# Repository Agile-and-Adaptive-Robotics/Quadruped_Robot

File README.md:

# AARL Quadruped Robot - Muscle Mutt

## Summary
This repository contains files relevant to the design, analysis, and testing of AARL's canine-inspired quadruped robot named Muscle Mutt.  Our goal in developing Muscle Mutt is for it to serve as a biologically relevant platform for testing embodied synthetic nervous systems pertaining to legged locomotion.  Toward this end, Muscle Mutt features body proportions similar to that of a Whippet, antagonistic pairs of braided pneumatic actuators (BPAs) that serve as proxies for muscles, and a CPG based neural control scheme.  All aspects of Muscle Mutt's design are under active development, including adjusting passive limb dynamics to be congruent with animal models, updating the electrical subsystem to incorporate a wider array of biologically relevant sensory feedback, and designing neural algorithms to generate stable and robust locomotion.

## References
More details on the design and testing of Muscle Mutt can be found in our associated papers.
```
@article{
C. W. Scharzenberger, “Design of a Canine Inspired Quadruped Robot as a Platform for Synthetic Neural Network Control,” Master’s Thesis, Portland State University, Digital, 2019. Accessed: Jun. 18, 2023. [Online]. Available: https://www.proquest.com/docview/2289587100?pq-origsite=gscholar&fromopenview=true
}
```
[Link to paper](https://pdxscholar.library.pdx.edu/cgi/viewcontent.cgi?article=6210&context=open_access_etds)

## Install Instructions
As a comprehensive robotics project, this repository contains information pertaining to three major areas of product development, including: (1) mechanical design, (2) electrical design, and (3) software.  The mechancial design for this project has been completed in Solidworks, while the electrical design has been completed in Eagle.  High level control software has primarily been developed in Matlab, though more recent efforts have been conducted in Python.  Requiste python modules are provided in requirement files in relevant directories.

## Repository Organization
This repository is organized into six primary directories, including: (1) Animatlab, (2) CAD_Electrical, (3) CAD_Mechanical, (4) Code, (5) Documentation, and (6) Manufacturing.  The names of these directories are largely self explanatory, with Animatlab neuromechanical simulations being stored in the Animatlab folder; Eagle CAD documents in the CAD_Electrical folder; Solidworks CAD documents in the CAD_Mechanical folder; Matlab, Python, and C code in the Code folder; supporting documentation and datasheets in the Documentation folder; and 3D printing documentation in the Manufacturing folder.

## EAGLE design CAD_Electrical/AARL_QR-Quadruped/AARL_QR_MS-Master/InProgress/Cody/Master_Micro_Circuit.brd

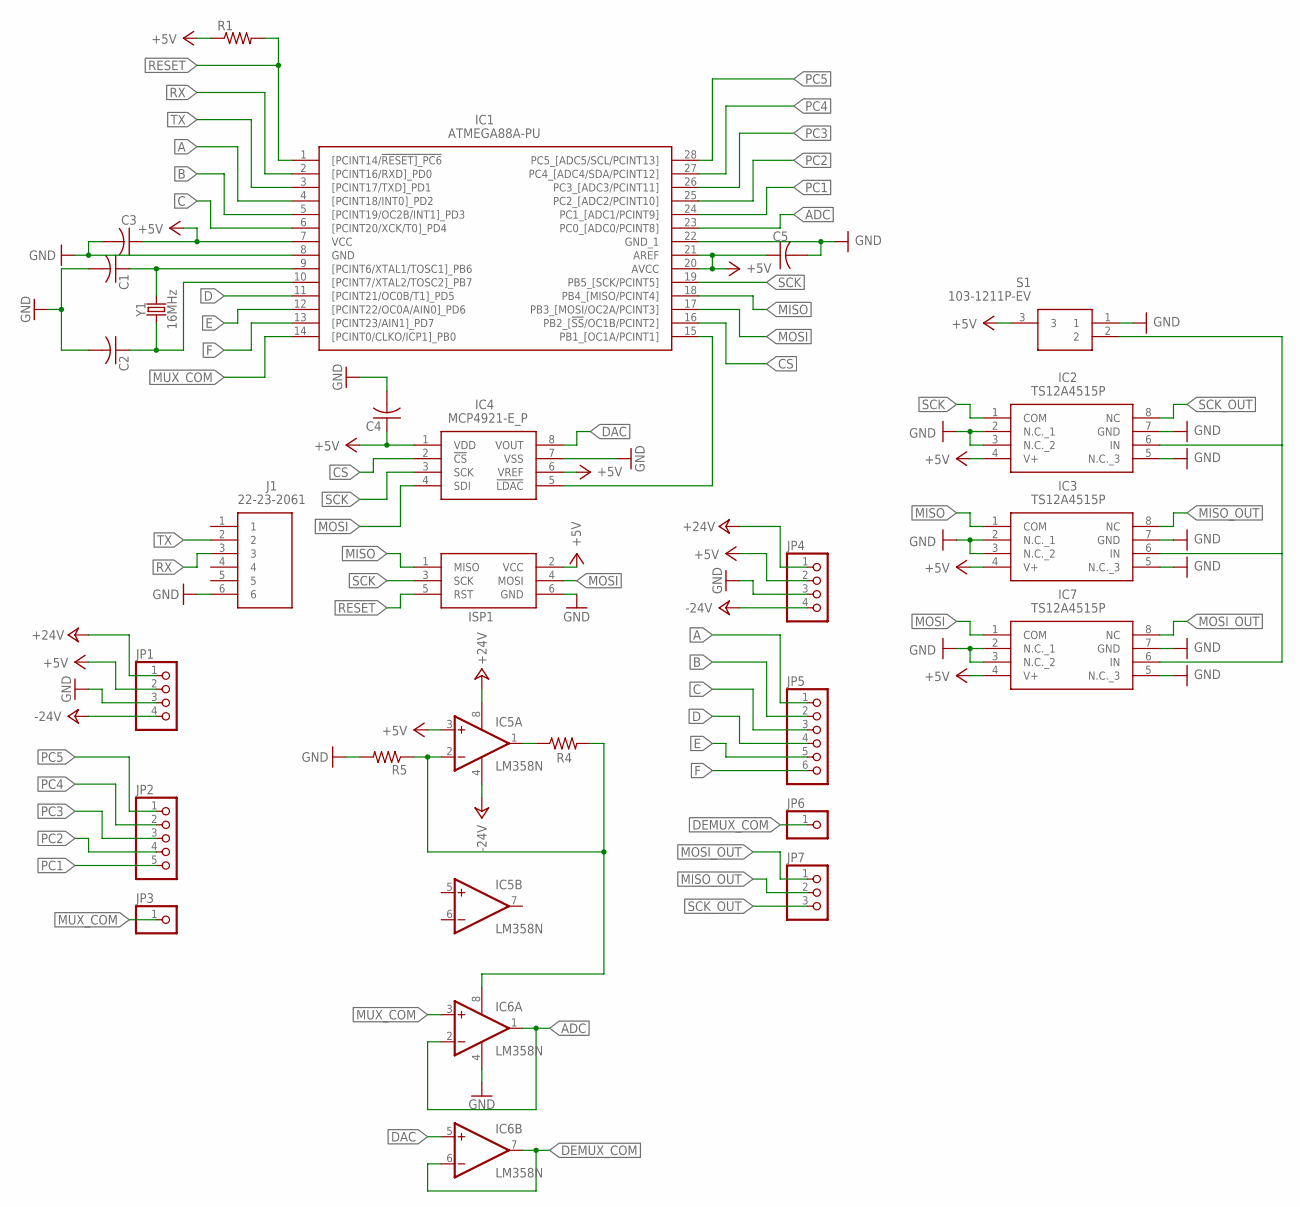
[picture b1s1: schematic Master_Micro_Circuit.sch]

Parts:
C1, C2, C3, C4, C5: C-US050-030X075; C050-030X075
IC1: ATMEGA88A-PU; DIP794W53P254L3467H457Q28N
IC2, IC3, IC7: TS12A4515P; DIP794W46P254L959H508Q8N
IC4: MCP4921-E_P; DIP781W56P254L950H533Q8N
IC5, IC6: LM358N; DIL08
ISP1: AVRISP-BOX
J1: 22-23-2061; SHDR6W87P0X254_1X6_1509X635X10
JP1, JP4: PINHD-1X4; 1X04
JP2: PINHD-1X5; 1X05
JP3, JP6: PINHD-1X1; 1X01
JP5: PINHD-1X6; 1X06
JP7: PINHD-1X3; 1X03
R1, R4, R5: R-US_0207/10; 0207/10
S1: 103-1211P-EV; 1031211PEV
Y1: 16MHz; HC49US

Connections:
+5V: C3.1, C4.1, C5.1, IC1.7 (VCC), IC1.20 (AVCC), IC1.21 (AREF), IC2.4 (V+), IC3.4 (V+), IC4.1 (VDD), IC4.6 (VREF), IC5.3 (+IN), IC7.4 (V+), ISP1.2 (VCC), JP1.2, JP4.2, R1.1, S1.3
+24V: IC5.8 (V+), JP1.1, JP4.1
-24V: IC5.4 (V-), JP1.4, JP4.4
A: IC1.4 ([PCINT18/INT0]_PD2), JP5.1
ADC: IC1.23 (PC0_[ADC0/PCINT8]), IC6.1 (OUT), IC6.2 (-IN)
B: IC1.5 ([PCINT19/OC2B/INT1]_PD3), JP5.2
C: IC1.6 ([PCINT20/XCK/T0]_PD4), JP5.3
CS: IC1.16 (PB2_[!SS!/OC1B/PCINT2]), IC4.2 (!CS)
D: IC1.11 ([PCINT21/OC0B/T1]_PD5), JP5.4
DAC: IC4.8 (VOUT), IC6.5 (+IN)
DEMUX_COM: IC6.6 (-IN), IC6.7 (OUT), JP6.1
E: IC1.12 ([PCINT22/OC0A/AIN0]_PD6), JP5.5
F: IC1.13 ([PCINT23/AIN1]_PD7), JP5.6
GND: C1.2, C2.2, C3.2, C4.2, C5.2, IC1.8 (GND), IC1.22 (GND_1), IC2.2 (N.C._1), IC2.3 (N.C._2), IC2.5 (N.C._3), IC2.7 (GND), IC3.2 (N.C._1), IC3.3 (N.C._2), IC3.5 (N.C._3), IC3.7 (GND), IC4.7 (VSS), IC6.4 (V-), IC7.2 (N.C._1), IC7.3 (N.C._2), IC7.5 (N.C._3), IC7.7 (GND), ISP1.6 (GND), J1.6, JP1.3, JP4.3, R5.2, S1.1
MISO: IC1.18 (PB4_[MISO/PCINT4]), IC3.1 (COM), ISP1.1 (MISO)
MISO_OUT: IC3.8 (NC), JP7.2
MOSI: IC1.17 (PB3_[MOSI/OC2A/PCINT3]), IC4.4 (SDI), IC7.1 (COM), ISP1.4 (MOSI)
MOSI_OUT: IC7.8 (NC), JP7.1
MUX_COM: IC1.14 ([PCINT0/CLKO/ICP1]_PB0), IC6.3 (+IN), JP3.1
unnamed: C2.1, IC1.10 ([PCINT7/XTAL2/TOSC2]_PB7), Y1.1
unnamed: IC5.1 (OUT), R4.1
unnamed: IC2.6 (IN), IC3.6 (IN), IC7.6 (IN), S1.2
unnamed: IC5.2 (-IN), IC6.8 (V+), R4.2, R5.1
unnamed: IC1.15 (PB1_[OC1A/PCINT1]), IC4.5 (!LDAC)
unnamed: C1.1, IC1.9 ([PCINT6/XTAL1/TOSC1]_PB6), Y1.2
PC1: IC1.24 (PC1_[ADC1/PCINT9]), JP2.5
PC2: IC1.25 (PC2_[ADC2/PCINT10]), JP2.4
PC3: IC1.26 (PC3_[ADC3/PCINT11]), JP2.3
PC4: IC1.27 (PC4_[ADC4/SDA/PCINT12]), JP2.2
PC5: IC1.28 (PC5_[ADC5/SCL/PCINT13]), JP2.1
RESET: IC1.1 ([PCINT14/!RESET]_PC6), ISP1.5 (RST), R1.2
RX: IC1.2 ([PCINT16/RXD]_PD0), J1.3
SCK: IC1.19 (PB5_[SCK/PCINT5]), IC2.1 (COM), IC4.3 (SCK), ISP1.3 (SCK)
SCK_OUT: IC2.8 (NC), JP7.3
TX: IC1.3 ([PCINT17/TXD]_PD1), J1.2

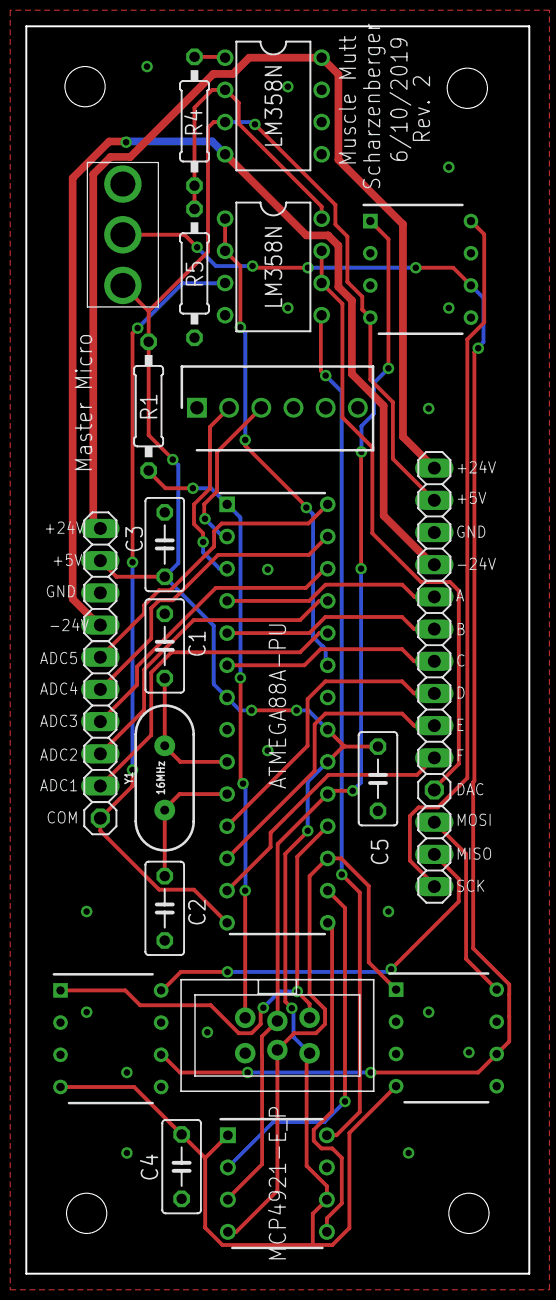
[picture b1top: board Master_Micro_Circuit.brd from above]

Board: 2 copper layers, 39.7 x 98.4 mm, 26 parts (0 on the bottom side), 35 nets.

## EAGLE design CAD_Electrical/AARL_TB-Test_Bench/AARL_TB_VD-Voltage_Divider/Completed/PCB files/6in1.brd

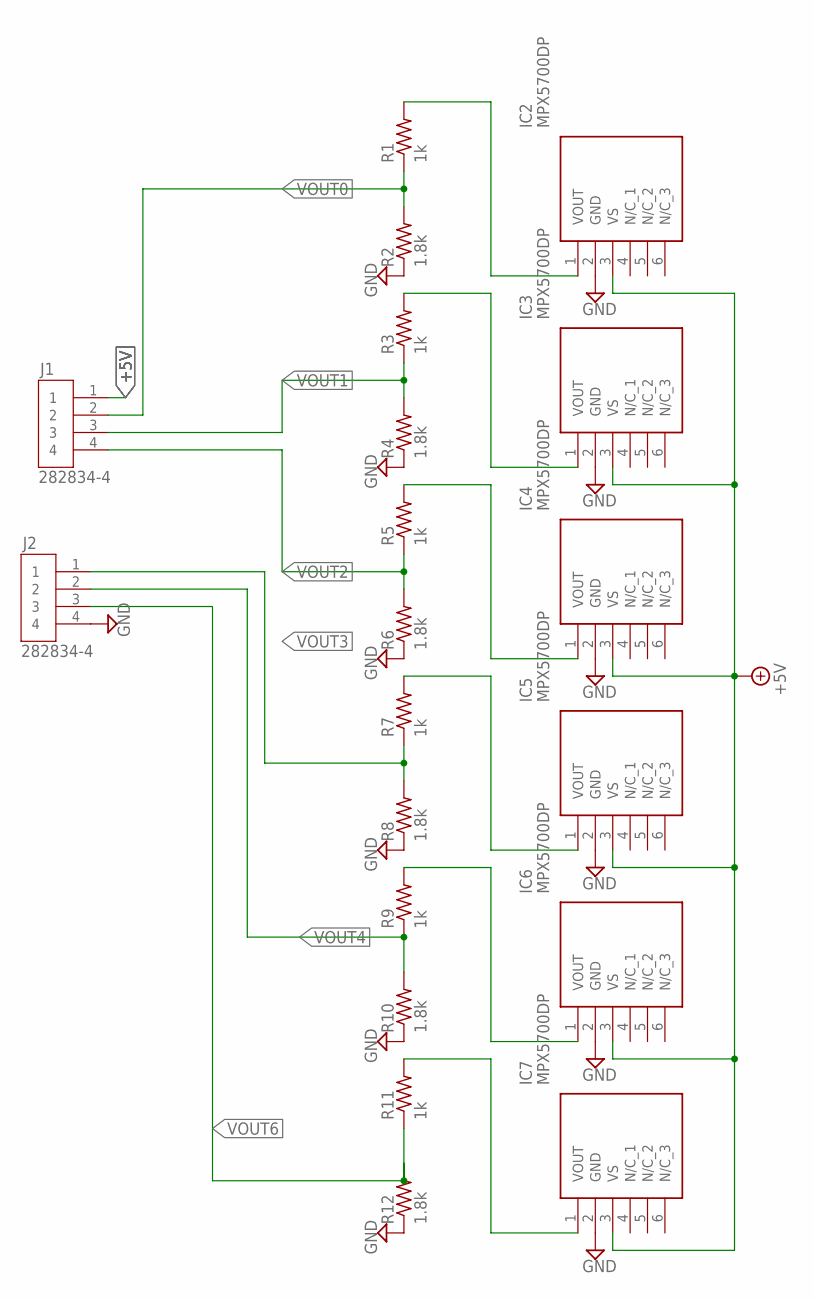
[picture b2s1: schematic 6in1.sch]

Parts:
IC2, IC3, IC4, IC5, IC6, IC7: MPX5700DP
J1, J2: 282834-4; HDRV4W85P254_4X1_1062X650X1000
R1, R3, R5, R7, R9, R11: 1k; 0204V
R2, R4, R6, R8, R10, R12: 1.8k; 0204V

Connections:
+5V: IC2.3 (VS), IC3.3 (VS), IC4.3 (VS), IC5.3 (VS), IC6.3 (VS), IC7.3 (VS), J1.1
GND: IC2.2 (GND), IC3.2 (GND), IC4.2 (GND), IC5.2 (GND), IC6.2 (GND), IC7.2 (GND), J2.4, R2.1, R4.1, R6.1, R8.1, R10.1, R12.1
unnamed: IC2.1 (VOUT), R1.2
unnamed: IC3.1 (VOUT), R3.2
unnamed: IC4.1 (VOUT), R5.2
unnamed: IC5.1 (VOUT), R7.2
unnamed: IC6.1 (VOUT), R9.2
unnamed: IC7.1 (VOUT), R11.2
VOUT0: J1.2, R1.1, R2.2
VOUT1: J1.3, R3.1, R4.2
VOUT2: J1.4, R5.1, R6.2
VOUT3: J2.1, R7.1, R8.2
VOUT4: J2.2, R9.1, R10.2
VOUT6: J2.3, R11.1, R12.2

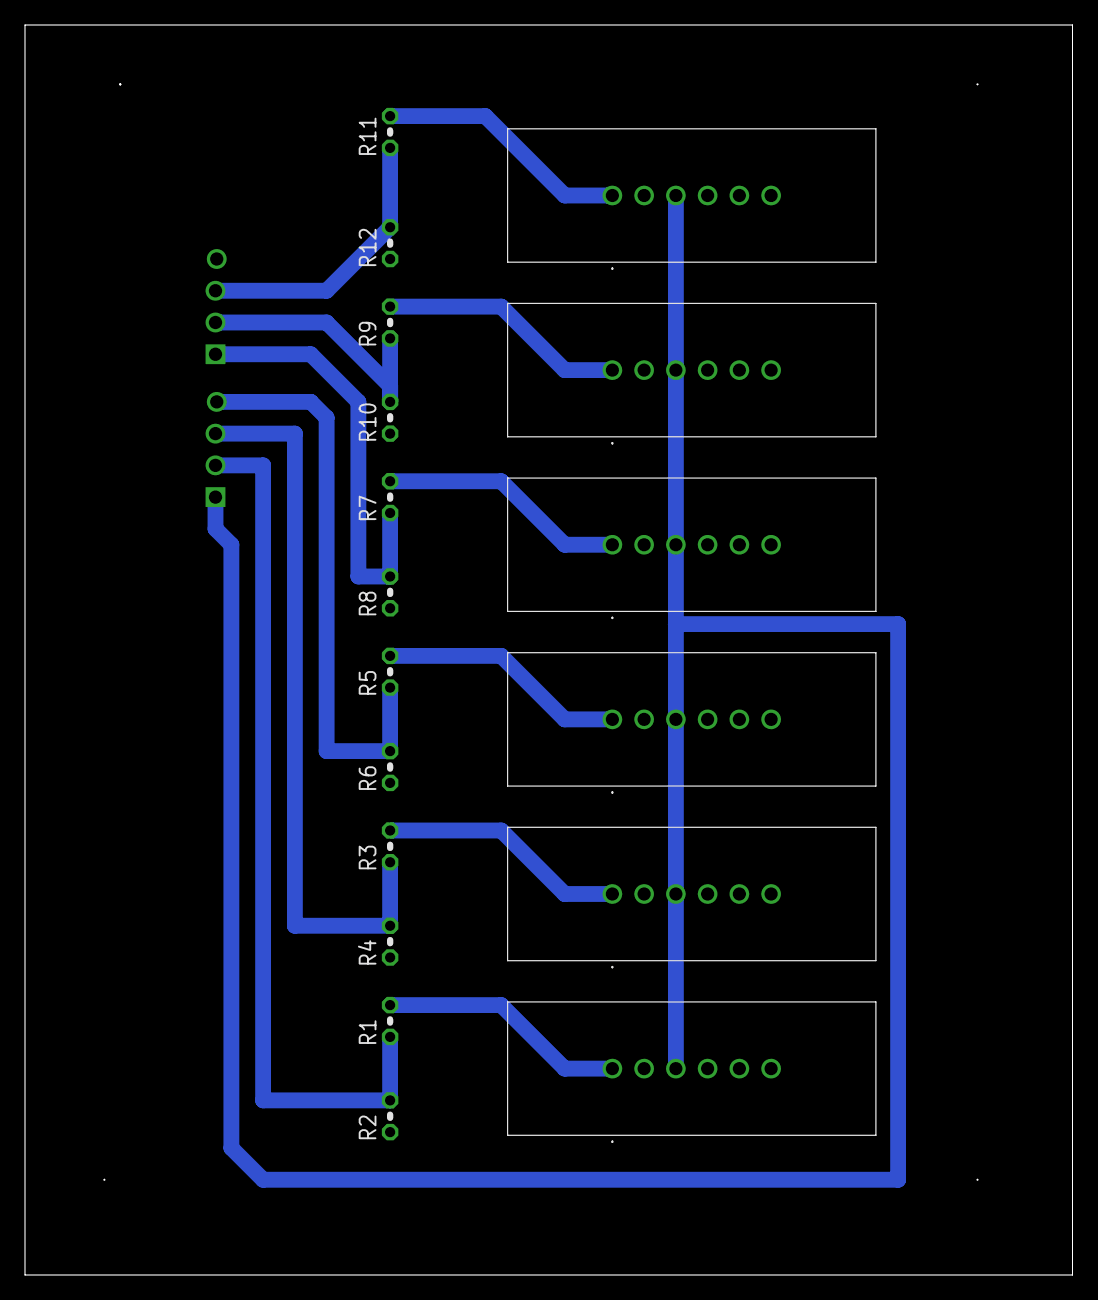
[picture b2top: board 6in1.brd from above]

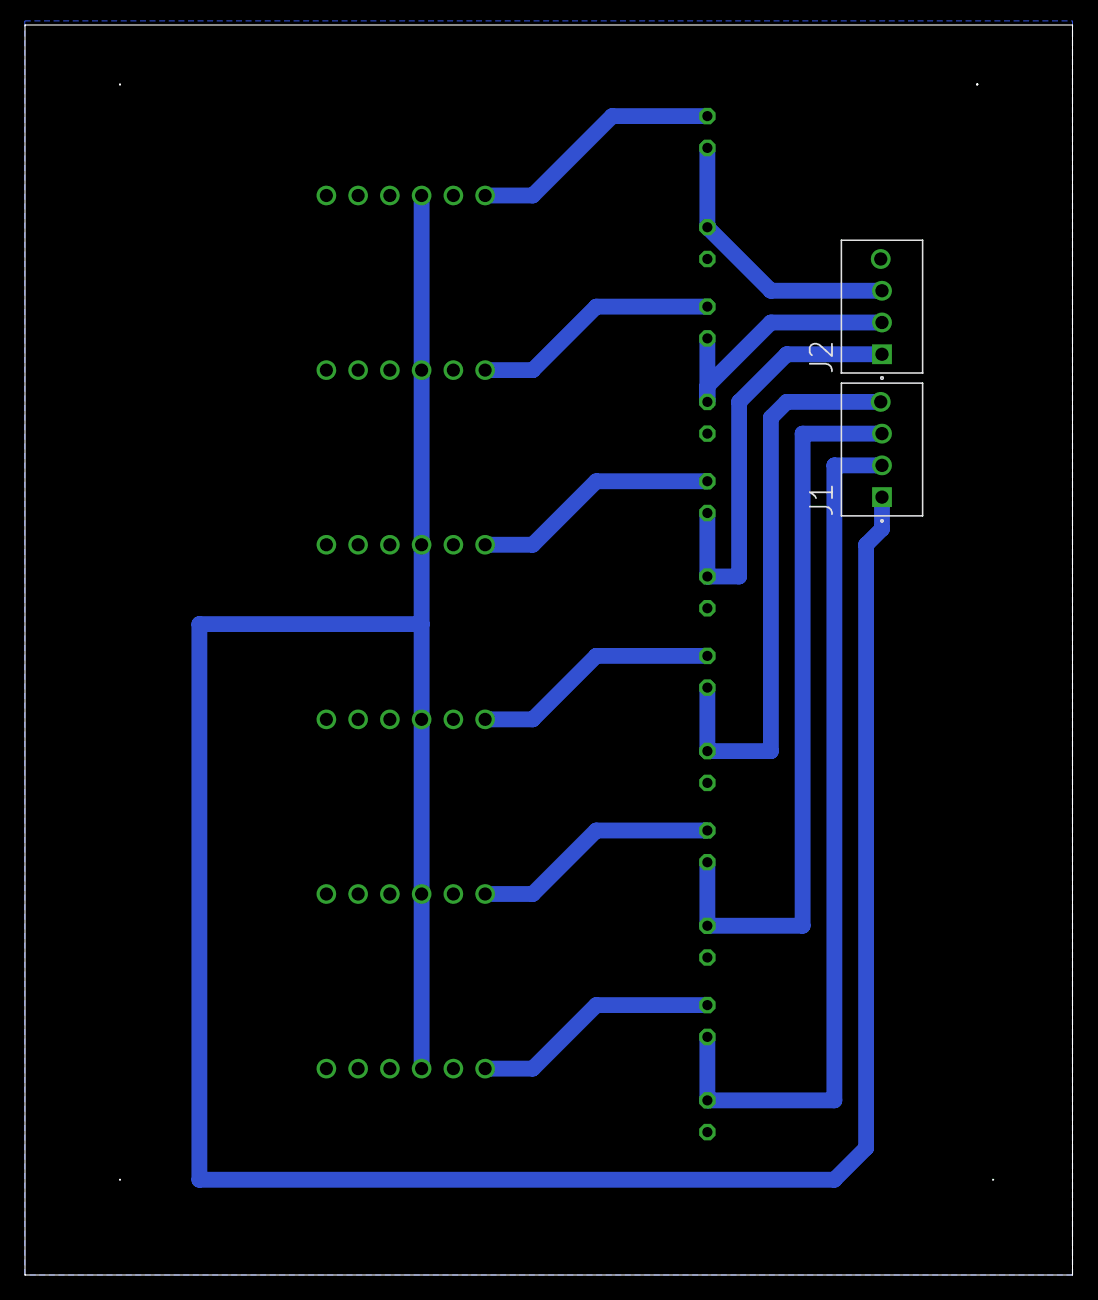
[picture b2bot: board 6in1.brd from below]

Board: 2 copper layers, 83.8 x 100.0 mm, 20 parts (2 on the bottom side), 14 nets.

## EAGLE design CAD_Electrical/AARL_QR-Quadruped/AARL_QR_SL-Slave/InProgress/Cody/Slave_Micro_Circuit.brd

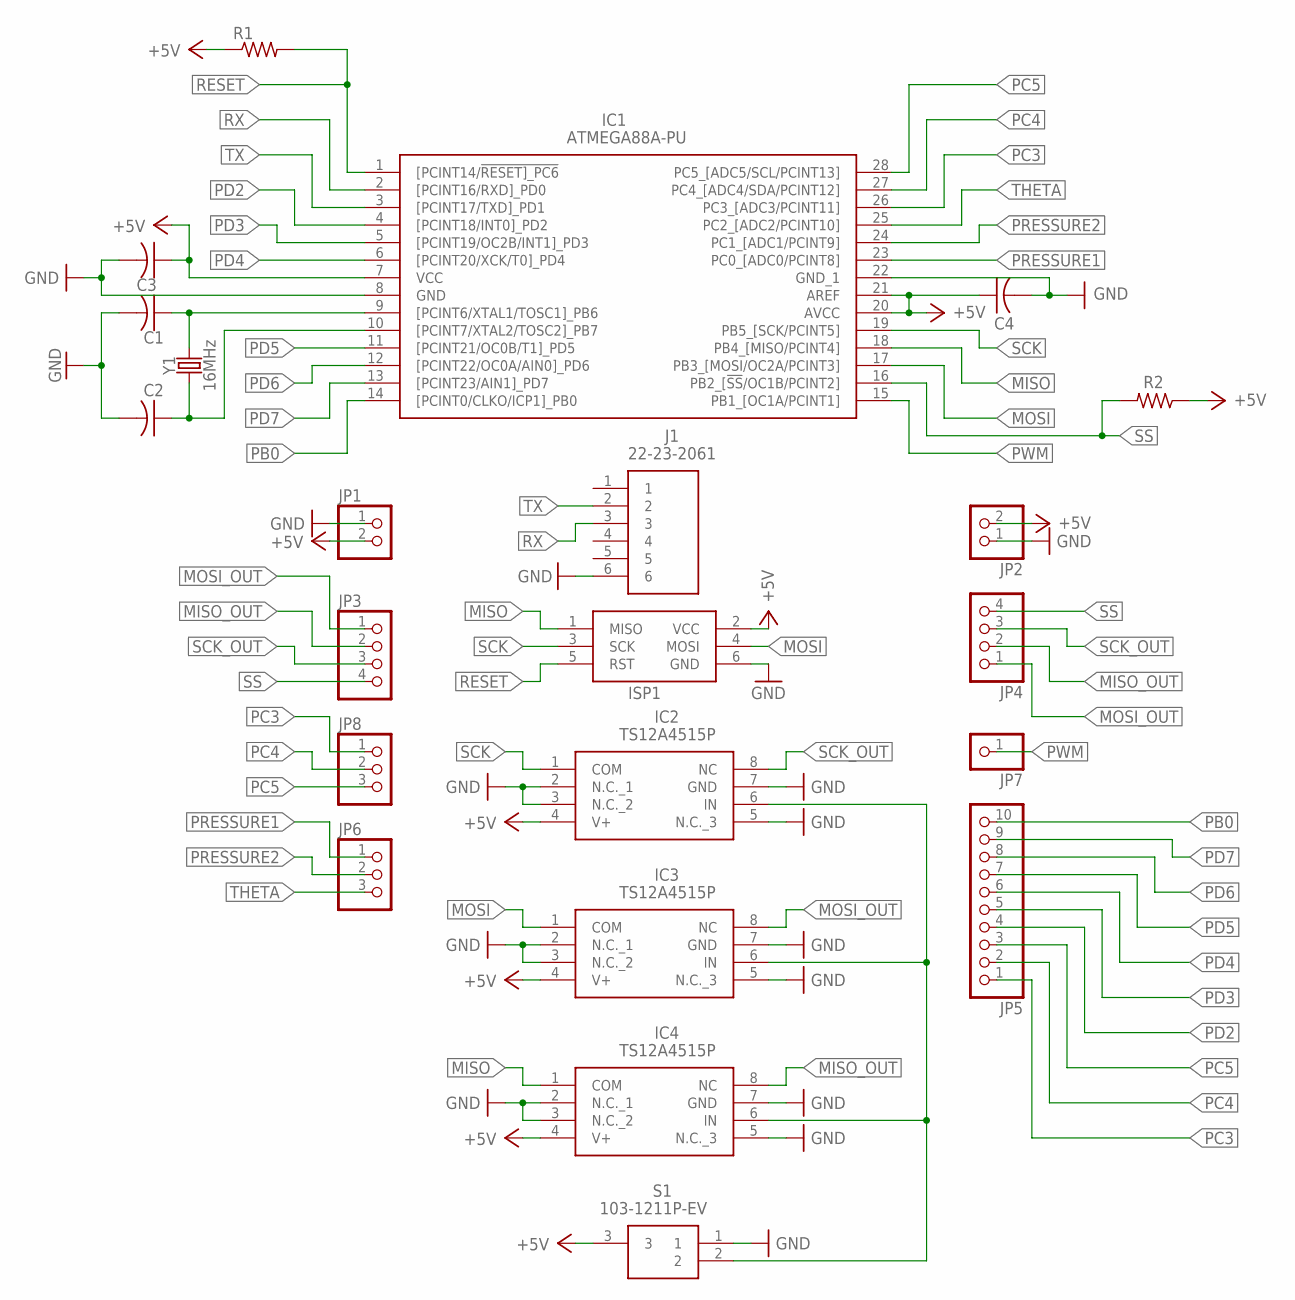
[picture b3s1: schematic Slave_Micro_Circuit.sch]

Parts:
C1, C2, C3, C4: C-US050-030X075; C050-030X075
IC1: ATMEGA88A-PU; DIP794W53P254L3467H457Q28N
IC2, IC3, IC4: TS12A4515P; DIP794W46P254L959H508Q8N
ISP1: AVRISP-BOX
J1: 22-23-2061; SHDR6W87P0X254_1X6_1509X635X10
JP1, JP2: PINHD-1X2; 1X02
JP3, JP4: PINHD-1X4; 1X04
JP5: PINHD-1X10; 1X10
JP6, JP8: PINHD-1X3; 1X03
JP7: PINHD-1X1; 1X01
R1, R2: R-US_0207/10; 0207/10
S1: 103-1211P-EV; 1031211PEV
Y1: 16MHz; HC49US

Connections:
+5V: C3.1, C4.1, IC1.7 (VCC), IC1.20 (AVCC), IC1.21 (AREF), IC2.4 (V+), IC3.4 (V+), IC4.4 (V+), ISP1.2 (VCC), JP1.2, JP2.2, R1.1, R2.1, S1.3
GND: C1.2, C2.2, C3.2, C4.2, IC1.8 (GND), IC1.22 (GND_1), IC2.2 (N.C._1), IC2.3 (N.C._2), IC2.5 (N.C._3), IC2.7 (GND), IC3.2 (N.C._1), IC3.3 (N.C._2), IC3.5 (N.C._3), IC3.7 (GND), IC4.2 (N.C._1), IC4.3 (N.C._2), IC4.5 (N.C._3), IC4.7 (GND), ISP1.6 (GND), J1.6, JP1.1, JP2.1, S1.1
MISO: IC1.18 (PB4_[MISO/PCINT4]), IC4.1 (COM), ISP1.1 (MISO)
MISO_OUT: IC4.8 (NC), JP3.2, JP4.2
MOSI: IC1.17 (PB3_[MOSI/OC2A/PCINT3]), IC3.1 (COM), ISP1.4 (MOSI)
MOSI_OUT: IC3.8 (NC), JP3.1, JP4.1
unnamed: IC2.6 (IN), IC3.6 (IN), IC4.6 (IN), S1.2
unnamed: C2.1, IC1.10 ([PCINT7/XTAL2/TOSC2]_PB7), Y1.1
unnamed: C1.1, IC1.9 ([PCINT6/XTAL1/TOSC1]_PB6), Y1.2
PB0: IC1.14 ([PCINT0/CLKO/ICP1]_PB0), JP5.10
PC3: IC1.26 (PC3_[ADC3/PCINT11]), JP5.1, JP8.1
PC4: IC1.27 (PC4_[ADC4/SDA/PCINT12]), JP5.2, JP8.2
PC5: IC1.28 (PC5_[ADC5/SCL/PCINT13]), JP5.3, JP8.3
PD2: IC1.4 ([PCINT18/INT0]_PD2), JP5.4
PD3: IC1.5 ([PCINT19/OC2B/INT1]_PD3), JP5.5
PD4: IC1.6 ([PCINT20/XCK/T0]_PD4), JP5.6
PD5: IC1.11 ([PCINT21/OC0B/T1]_PD5), JP5.7
PD6: IC1.12 ([PCINT22/OC0A/AIN0]_PD6), JP5.8
PD7: IC1.13 ([PCINT23/AIN1]_PD7), JP5.9
PRESSURE1: IC1.23 (PC0_[ADC0/PCINT8]), JP6.1
PRESSURE2: IC1.24 (PC1_[ADC1/PCINT9]), JP6.2
PWM: IC1.15 (PB1_[OC1A/PCINT1]), JP7.1
RESET: IC1.1 ([PCINT14/!RESET]_PC6), ISP1.5 (RST), R1.2
RX: IC1.2 ([PCINT16/RXD]_PD0), J1.3
SCK: IC1.19 (PB5_[SCK/PCINT5]), IC2.1 (COM), ISP1.3 (SCK)
SCK_OUT: IC2.8 (NC), JP3.3, JP4.3
SS: IC1.16 (PB2_[!SS!/OC1B/PCINT2]), JP3.4, JP4.4, R2.2
THETA: IC1.25 (PC2_[ADC2/PCINT10]), JP6.3
TX: IC1.3 ([PCINT17/TXD]_PD1), J1.2

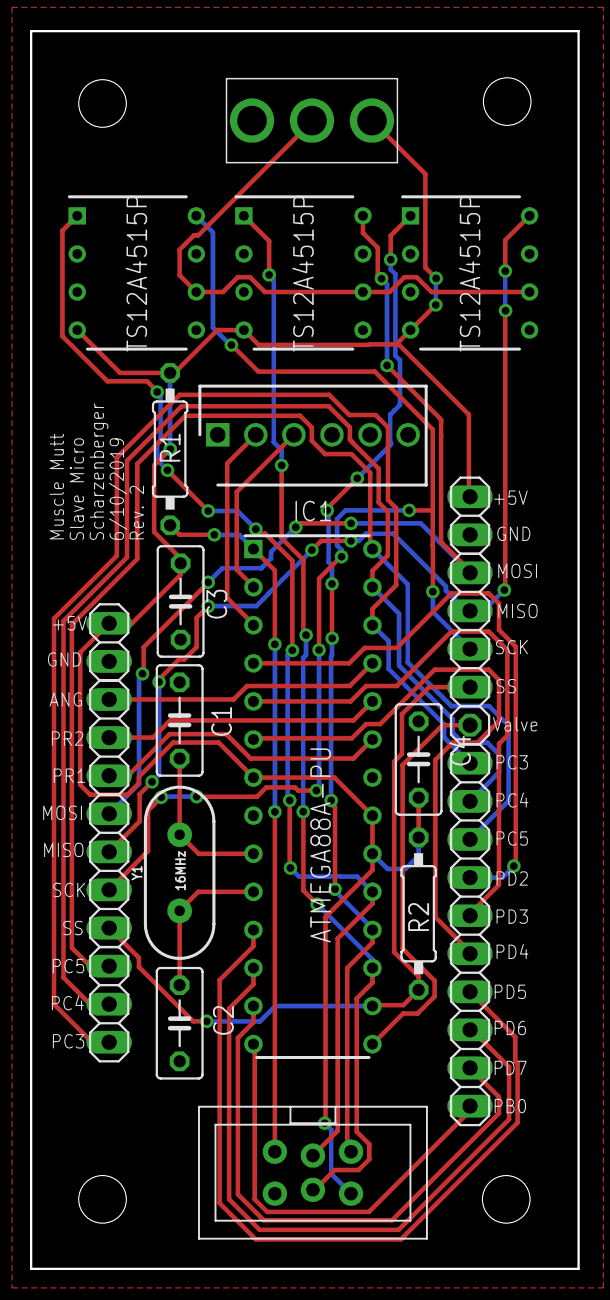
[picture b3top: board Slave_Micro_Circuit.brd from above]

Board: 2 copper layers, 36.5 x 82.5 mm, 22 parts (0 on the bottom side), 29 nets.

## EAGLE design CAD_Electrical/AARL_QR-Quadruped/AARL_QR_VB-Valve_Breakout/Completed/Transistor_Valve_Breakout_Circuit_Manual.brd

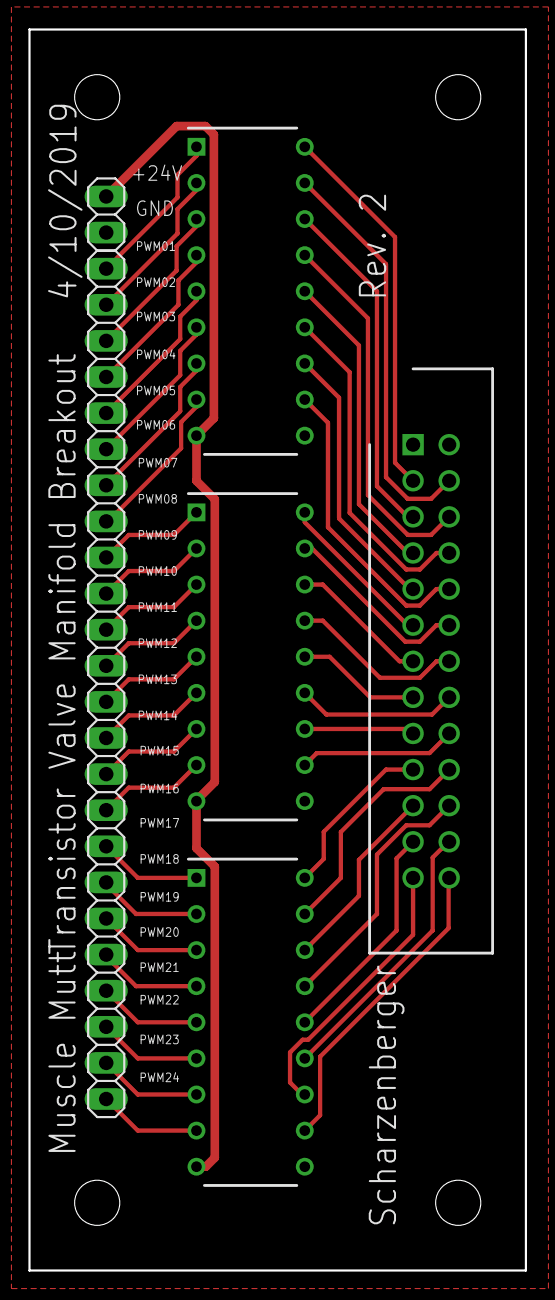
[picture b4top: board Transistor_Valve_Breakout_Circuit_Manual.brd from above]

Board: 2 copper layers, 34.9 x 87.3 mm, 6 parts (0 on the bottom side), 50 nets.

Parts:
IC1, IC2, IC3: TBD62783APG; DIP762W55P254L2286H480Q18N
J1: 30326-6002HB; SHDR26W81P254_2X13_4060X840X94
JP1: 1X24
JP2: 1X02

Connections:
+24V: IC1.9, IC2.9, IC3.9, JP2.1
GND: IC1.10, IC2.10, IC3.10, J1.2, JP2.2
PWM01: IC1.1, JP1.1
PWM02: IC1.2, JP1.2
PWM03: IC1.3, JP1.3
PWM04: IC1.4, JP1.4
PWM05: IC1.5, JP1.5
PWM06: IC1.6, JP1.6
PWM07: IC1.7, JP1.7
PWM08: IC1.8, JP1.8
PWM09: IC2.1, JP1.9
PWM10: IC2.2, JP1.10
PWM11: IC2.3, JP1.11
PWM12: IC2.4, JP1.12
PWM13: IC2.5, JP1.13
PWM14: IC2.6, JP1.14
PWM15: IC2.7, JP1.15
PWM16: IC2.8, JP1.16
PWM17: IC3.1, JP1.17
PWM18: IC3.2, JP1.18
PWM19: IC3.3, JP1.19
PWM20: IC3.4, JP1.20
PWM21: IC3.5, JP1.21
PWM22: IC3.6, JP1.22
PWM23: IC3.7, JP1.23
PWM24: IC3.8, JP1.24
VALVE01: IC1.18, J1.3
VALVE02: IC1.17, J1.4
VALVE03: IC1.16, J1.5
VALVE04: IC1.15, J1.6
VALVE05: IC1.14, J1.7
VALVE06: IC1.13, J1.8
VALVE07: IC1.12, J1.9
VALVE08: IC1.11, J1.10
VALVE09: IC2.18, J1.11
VALVE10: IC2.17, J1.12
VALVE11: IC2.16, J1.13
VALVE12: IC2.15, J1.14
VALVE13: IC2.14, J1.15
VALVE14: IC2.13, J1.16
VALVE15: IC2.12, J1.17
VALVE16: IC2.11, J1.18
VALVE17: IC3.18, J1.19
VALVE18: IC3.17, J1.20
VALVE19: IC3.16, J1.21
VALVE20: IC3.15, J1.22
VALVE21: IC3.14, J1.23
VALVE22: IC3.13, J1.24
VALVE23: IC3.12, J1.25
VALVE24: IC3.11, J1.26

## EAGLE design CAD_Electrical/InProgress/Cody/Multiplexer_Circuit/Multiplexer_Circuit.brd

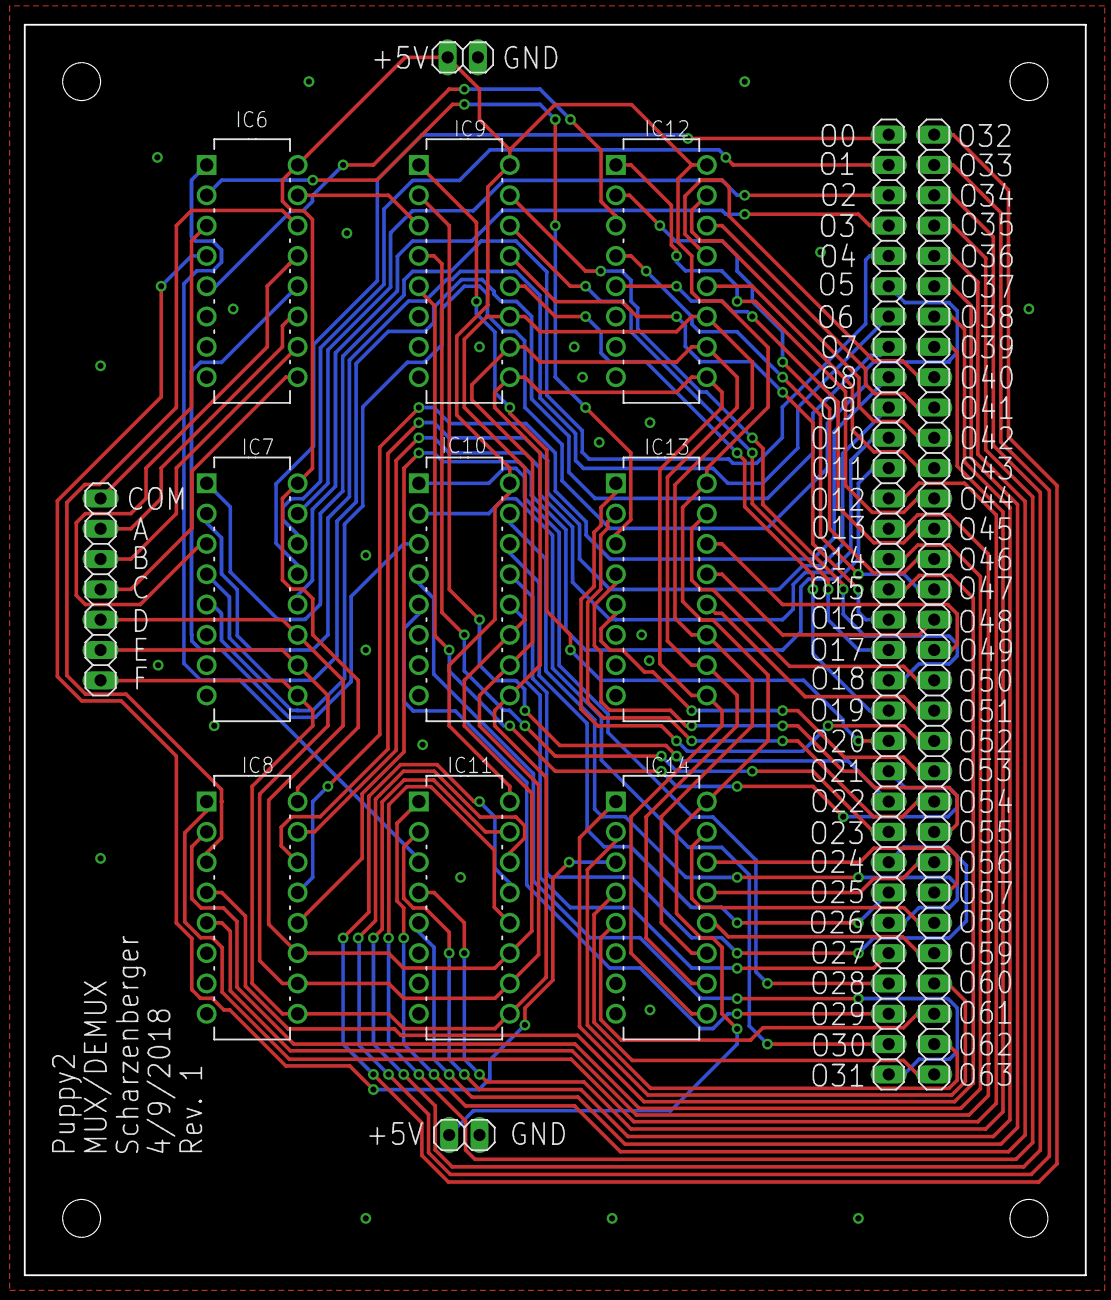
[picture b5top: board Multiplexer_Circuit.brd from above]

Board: 2 copper layers, 88.9 x 104.8 mm, 16 parts (0 on the bottom side), 81 nets.

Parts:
IC6, IC7, IC8, IC9, IC10, IC11, IC12, IC13, IC14: CD4051BE; DIP254P762X508-16
JP1, JP2, JP3, JP4: 1X16
JP5, JP6: 1X02
JP7: 1X07

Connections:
+5V: IC6.16, IC7.16, IC8.16, IC9.16, IC10.16, IC11.16, IC12.16, IC13.16, IC14.16, JP5.1, JP6.1
A0: IC6.11, JP7.2
B0: IC6.10, JP7.3
C0: IC6.9, JP7.4
D0: IC7.11, IC8.11, IC9.11, IC10.11, IC11.11, IC12.11, IC13.11, IC14.11, JP7.5
E0: IC7.10, IC8.10, IC9.10, IC10.10, IC11.10, IC12.10, IC13.10, IC14.10, JP7.6
F0: IC7.9, IC8.9, IC9.9, IC10.9, IC11.9, IC12.9, IC13.9, IC14.9, JP7.7
GND: IC6.6, IC6.7, IC6.8, IC7.6, IC7.7, IC7.8, IC8.6, IC8.7, IC8.8, IC9.6, IC9.7, IC9.8, IC10.6, IC10.7, IC10.8, IC11.6, IC11.7, IC11.8, IC12.6, IC12.7, IC12.8, IC13.6, IC13.7, IC13.8, IC14.6, IC14.7, IC14.8, JP5.2, JP6.2
MUX00: IC7.13, JP1.16
MUX01: IC7.14, JP1.15
MUX02: IC7.15, JP1.14
MUX03: IC7.12, JP1.13
MUX04: IC7.1, JP1.12
MUX05: IC7.5, JP1.11
MUX06: IC7.2, JP1.10
MUX07: IC7.4, JP1.9
MUX08: IC8.13, JP1.8
MUX09: IC8.14, JP1.7
MUX10: IC8.15, JP1.6
MUX11: IC8.12, JP1.5
MUX12: IC8.1, JP1.4
MUX13: IC8.5, JP1.3
MUX14: IC8.2, JP1.2
MUX15: IC8.4, JP1.1
MUX16: IC9.13, JP2.16
MUX17: IC9.14, JP2.15
MUX18: IC9.15, JP2.14
MUX19: IC9.12, JP2.13
MUX20: IC9.1, JP2.12
MUX21: IC9.5, JP2.11
MUX22: IC9.2, JP2.10
MUX23: IC9.4, JP2.9
MUX24: IC10.13, JP2.8
MUX25: IC10.14, JP2.7
MUX26: IC10.15, JP2.6
MUX27: IC10.12, JP2.5
MUX28: IC10.1, JP2.4
MUX29: IC10.5, JP2.3
MUX30: IC10.2, JP2.2
MUX31: IC10.4, JP2.1
MUX32: IC11.13, JP3.16
MUX33: IC11.14, JP3.15
MUX34: IC11.15, JP3.14
MUX35: IC11.12, JP3.13
MUX36: IC11.1, JP3.12
MUX37: IC11.5, JP3.11
MUX38: IC11.2, JP3.10
MUX39: IC11.4, JP3.9
MUX40: IC12.13, JP3.8
MUX41: IC12.14, JP3.7
MUX42: IC12.15, JP3.6
MUX43: IC12.12, JP3.5
MUX44: IC12.1, JP3.4
MUX45: IC12.5, JP3.3
MUX46: IC12.2, JP3.2
MUX47: IC12.4, JP3.1
MUX48: IC13.13, JP4.16
MUX49: IC13.14, JP4.15
MUX50: IC13.15, JP4.14
MUX51: IC13.12, JP4.13
MUX52: IC13.1, JP4.12
MUX53: IC13.5, JP4.11
MUX54: IC13.2, JP4.10
MUX55: IC13.4, JP4.9
MUX56: IC14.13, JP4.8
MUX57: IC14.14, JP4.7
MUX58: IC14.15, JP4.6
MUX59: IC14.12, JP4.5
MUX60: IC14.1, JP4.4
MUX61: IC14.5, JP4.3
MUX62: IC14.2, JP4.2
MUX63: IC14.4, JP4.1
MUXOUT: IC6.3, JP7.1
unnamed: IC6.13, IC7.3
unnamed: IC6.14, IC8.3
unnamed: IC6.15, IC9.3
unnamed: IC6.12, IC10.3
unnamed: IC6.1, IC11.3
unnamed: IC6.5, IC12.3
unnamed: IC6.2, IC13.3
unnamed: IC6.4, IC14.3

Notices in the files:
parts and their libraries:
SparkFun-Clocks: Licensing: Creative Commons ShareAlike 4.0 International - https://creativecommons.org/licenses/by-sa/4.0
